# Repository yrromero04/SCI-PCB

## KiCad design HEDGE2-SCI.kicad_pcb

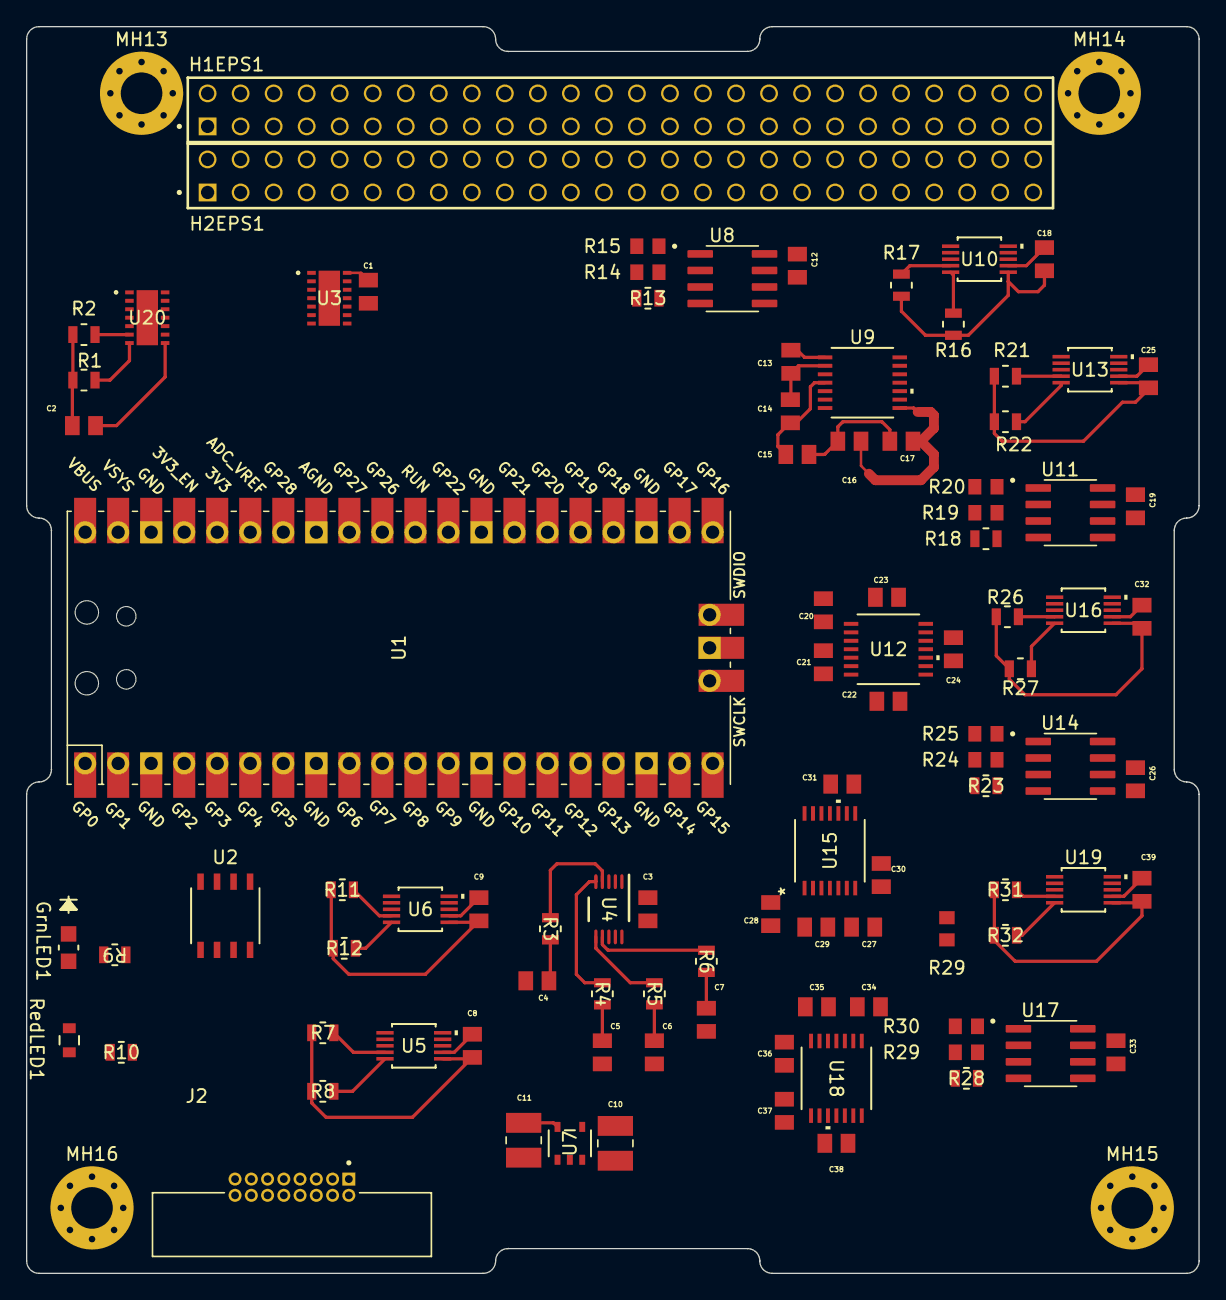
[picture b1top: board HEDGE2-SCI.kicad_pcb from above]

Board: 4 copper layers, 90.2 x 95.9 mm, 101 parts (0 on the bottom side), 66 nets.

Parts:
C1, C2, C3, C4, C5, C6, C7, C8, C9, C12, C13, C14, C15, C16, C17, C19, C20, C21, C22, C23, C24, C26, C27, C28, C29, C30, C31, C33, C34, C35, C36, C37, C38: 0.1uF; 0.1uF - CAPC2012X145N
C10, C11: 10uF; 10uF-CAPC3225X270N
C18, C25, C32, C39: 100nF; 0.1uF - CAPC2012X145N
GrnLED1: LTST-C170GKT; GrnLED - LED_LTST-C170GKT_LTO
H1EPS1, H2EPS1: Conn_02x26_Odd_Even; SAMTEC_ESQ-126-39-G-D
J2: G125-MH11605M3P; G125-MH11605M3P - HARWIN_G125-MH11605M3P
MH13, MH14, MH15, MH16: MountingHole_Pad; MountingHole_3.2mm_M3_Pad_Via
R1, R2: 60; 60ohm - STA_RMCF0805_STP-L
R3, R4, R5, R6: 4k; 4kOhm-STA_RMCF0805_STP-L
R7, R8, R11, R12, R13, R16, R17, R18, R21, R22, R23, R26, R27, R28, R31, R32: 10k; 10K-STA_RMCF0805_STP-L
R9, R10: 150; 150ohm-STA_RMCF0805_STP-L
R14, R15, R19, R20, R24, R25, R29, R29#2, R30: 1k; 1kOhm - RC0805N_VIS
RedLED1: LTST-C171KRKT; RedLED - LED_LTST-C171_LTO
U1: MC68332; PICO-RPi_Pico_SMD_TH
U2: SN65LBC176QDRQ1; SN65L-RS485-D8-L
U3: MCP2517FD-H/JHA; CAN_Controller_VDFN14_JHA_MCH-L
U4: ADS1118QDGSRQ1; ADS118-DGS0010A_L
U5, U6, U10, U13, U16, U19: INA238AQDGSRQ1; INA238A_TEX
U7: MAX1682EUK+T; MAXEUK-21-0057F_MXM-L
U8, U11, U14, U17: MAX6634MSA_T; MAX6634MSA - SOIC127P600X175-8N
U9, U12, U15, U18: MAX31856MUD+T; MAX-MUD+21-0066J_14_MXM-L
U20: TCAN1057AEVDRQ1-CAN_Driver; CAN-Driver_VDFN14_JHA_MCH-L

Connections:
3V3 EN: C1.1, U3.14 (VDD)
+3V3: C16.1, C17.1, C23.1, C24.1, C30.1, C31.1, C37.1, C38.1, U6.10 (IN+), U9.5 (AVDD), U9.8 (DVDD), U12.5 (AVDD), U12.8 (DVDD), U15.5 (AVDD), U15.8 (DVDD), U18.5 (AVDD), U18.8 (DVDD)
/EPS/5V_PERM: H1EPS1.25, H1EPS1.26, H2EPS1.25, H2EPS1.26
/EPS/BATT: H2EPS1.45, H2EPS1.46
/EPS/CHARGE: H2EPS1.43, H2EPS1.44
CSn_1: U1.1, U3.13 (nCS)
DIN_MOSI19: U1.19, U4.10 (DIN)
DRDY_MISO16: U1.16, U4.9 (DOUT_DRDY_N)
FAULT_GP12: U9.13 (*FAULT), U12.13 (*FAULT), U15.10 (SCK), U18.13 (*FAULT)
GND: C1.2, C2.2, C3.1, C4.2, C5.2, C6.2, C7.1, C10.2, C12.2, C13.2, C15.2, C16.2, C17.2, C19.2, C20.2, C22.2, C23.2, C24.2, C26.2, C27.2, C29.2, C30.2, C31.2, C33.2, C34.2, C36.2, C37.2, C38.2, GrnLED1.1, H1EPS1.29, H1EPS1.30, H1EPS1.31, H1EPS1.32, H2EPS1.29, H2EPS1.30, H2EPS1.31, H2EPS1.32, MH13.1, MH14.1, MH15.1, MH16.1, RedLED1.1, U2.5 (GND), U3.7 (VSS), U3.15 (VSS), U4.3 (GND), U5.1 (A1), U5.2 (A0), U5.9 (IN-), U6.2 (A0), U6.9 (IN-), U7.1 (GND), U8.4 (GND), U8.5 (A2), U8.6 (A1), U8.7 (A0), U9.1 (AGND), U9.14 (DGND), U10.1 (A1), U10.2 (A0), U11.4 (GND), U11.5 (A2), U11.6 (A1), U12.1 (AGND), U12.14 (DGND), U13.1 (A1), U14.4 (GND), U14.5 (A2), U14.7 (A0), U15.1 (AGND), U15.14 (DGND), U16.1 (A1), U17.4 (GND), U17.5 (A2), U18.1 (AGND), U18.14 (DGND), U19.1 (A1), U20.2 (GND), U20.8 (S)
GPIO_5: U1.5, U2.2 (*RE)
GPIO_6: U1.6, U2.3 (DE)
MOSI_3: U1.3, U3.11 (SDI)
M_DRDY: U9.7 (*DRDY), U12.7 (*DRDY), U15.7 (*DRDY), U18.7 (*DRDY)
unnamed: C2.1, R1.2, R2.1
unnamed: GrnLED1.2, R9.2
unnamed: R10.2, RedLED1.2
unnamed: R3.1, U4.4 (AIN0)
unnamed: R4.1, U4.5 (AIN1)
unnamed: R5.1, U4.6 (AIN2)
unnamed: R6.1, U4.7 (AIN3)
unnamed: C3.2, U4.8 (VDD), U5.10 (IN+)
unnamed: C8.1, U5.7 (GND)
unnamed: C8.2, R7.1, R8.1, U5.6 (VS)
unnamed: C9.1, U6.7 (GND)
unnamed: C9.2, R11.1, R12.1, U6.6 (VS)
unnamed: C11.1, U7.5 (C1+)
unnamed: C11.2, U7.3 (C1-)
unnamed: C4.1, C5.1, C6.1, C7.2, C10.1, J2.1, J2.2, J2.3, J2.4, J2.5, J2.6, J2.7, J2.8, J2.9, J2.10, J2.11, J2.12, J2.13, J2.14, J2.15, J2.16, R3.2, R4.2, R5.2, R6.2, U7.2 (OUT)
unnamed: C13.1, C14.1, U9.2 (BIAS), U9.3 (T-)
unnamed: C14.2, C15.1, U9.4 (T+)
unnamed: C18.1, U10.7 (GND)
unnamed: C18.2, R16.1, R17.2, U10.6 (VS)
unnamed: C20.1, C21.1, U12.2 (BIAS), U12.3 (T-)
unnamed: C21.2, C22.1, U12.4 (T+)
unnamed: C25.1, U13.7 (GND)
unnamed: C25.2, R21.1, R22.1, U13.6 (VS)
unnamed: C27.1, C28.1, U15.2 (BIAS), U15.3 (T-)
unnamed: C28.2, C29.1, U15.4 (T+)
unnamed: C32.1, U16.7 (GND)
unnamed: C32.2, R26.1, R27.1, U16.6 (VS)
unnamed: C34.1, C35.1, U18.2 (BIAS), U18.3 (T-)
unnamed: C35.2, C36.1, U18.4 (T+)
unnamed: C39.1, U19.7 (GND)
unnamed: C39.2, R31.1, R32.1, U19.6 (VS)
unnamed: R1.1, U20.7 (CANH)
unnamed: R2.2, U20.6 (CANL)
unnamed: U3.2 (RXCAN), U20.4 (RXD)
unnamed: U3.1 (TXCAN), U20.1 (TXD)
RX_8: U1.8, U2.1 (R)
SCK_2: U1.2, U3.10 (SCK)
SCK_22: U1.22, U9.10 (SCK), U12.10 (SCK), U15.12 (SDI), U18.10 (SCK)
SCLK_18: U1.18, U4.1 (SCLK)
SCL_1: R8.2, R12.2, R14.2, R19.2, R24.2, R29.2, U5.5 (SCL), U6.5 (SCL), U8.2 (SCL), U11.2 (SCL), U14.2 (SCL), U17.2 (SCL)
SCL_21: R16.2, R22.2, R27.2, R29#2.2, R32.2, U10.5 (SCL), U13.5 (SCL), U16.5 (SCL), U19.2 (A0), U19.5 (SCL)
SDA_0: R7.2, R11.2, R15.2, R20.2, R25.2, R30.2, U5.4 (SDA), U6.4 (SDA), U8.1 (SDA), U11.1 (SDA), U14.1 (SDA), U17.1 (SDA)
SDA_22: R17.1, R21.2, R26.2, R31.2, U10.4 (SDA), U13.4 (SDA), U16.2 (A0), U16.4 (SDA), U19.4 (SDA)
SDI_MOSI11: U9.12 (SDI), U12.12 (SDI), U15.11 (SDO), U18.12 (SDI)
SDO_MISO20: U9.11 (SDO), U12.11 (SDO), U15.13 (*FAULT), U18.11 (SDO)
TX_7: U1.7, U2.4 (D)
VBUS: U5.8 (VBUS), U6.1 (A1), U6.8 (VBUS), U7.4 (IN), U10.8 (VBUS), U13.2 (A0), U13.8 (VBUS), U16.8 (VBUS), U19.8 (VBUS)
alert: R13.2, R18.2, R23.2, R28.2, U8.3 (~ALERT), U11.3 (~ALERT), U14.3 (~ALERT), U17.3 (~ALERT)
gpio_int_4: U1.4, U3.4 (*INT)
pwr_sply: C12.1, C19.1, C26.1, C33.1, R13.1, R14.1, R15.1, R18.1, R19.1, R20.1, R23.1, R24.1, R25.1, R28.1, R29.1, R29#2.1, R30.1, U8.8 (VCC), U11.7 (A0), U11.8 (VCC), U14.6 (A1), U14.8 (VCC), U17.6 (A1), U17.7 (A0), U17.8 (VCC), U20.3 (VCC), U20.5 (VIO)
xtra_int: U3.8 (*INT1/GPIO1), U3.9 (*INT0/GPIO0/XSTBY)
~CS_GPI17: U1.17, U4.2 (CS_N)

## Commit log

2025-10-15 Revert "Add files via upload"
    This reverts commit 3488cd8e624d50297a5ebf3ac66df6df4d75d84a.
2025-10-15 Add files via upload
    Updated PCB
2025-10-16 Revert "Add files via upload"
    This reverts commit e967c964afbdcf55ad47b4a2726d82822f251f5c.
